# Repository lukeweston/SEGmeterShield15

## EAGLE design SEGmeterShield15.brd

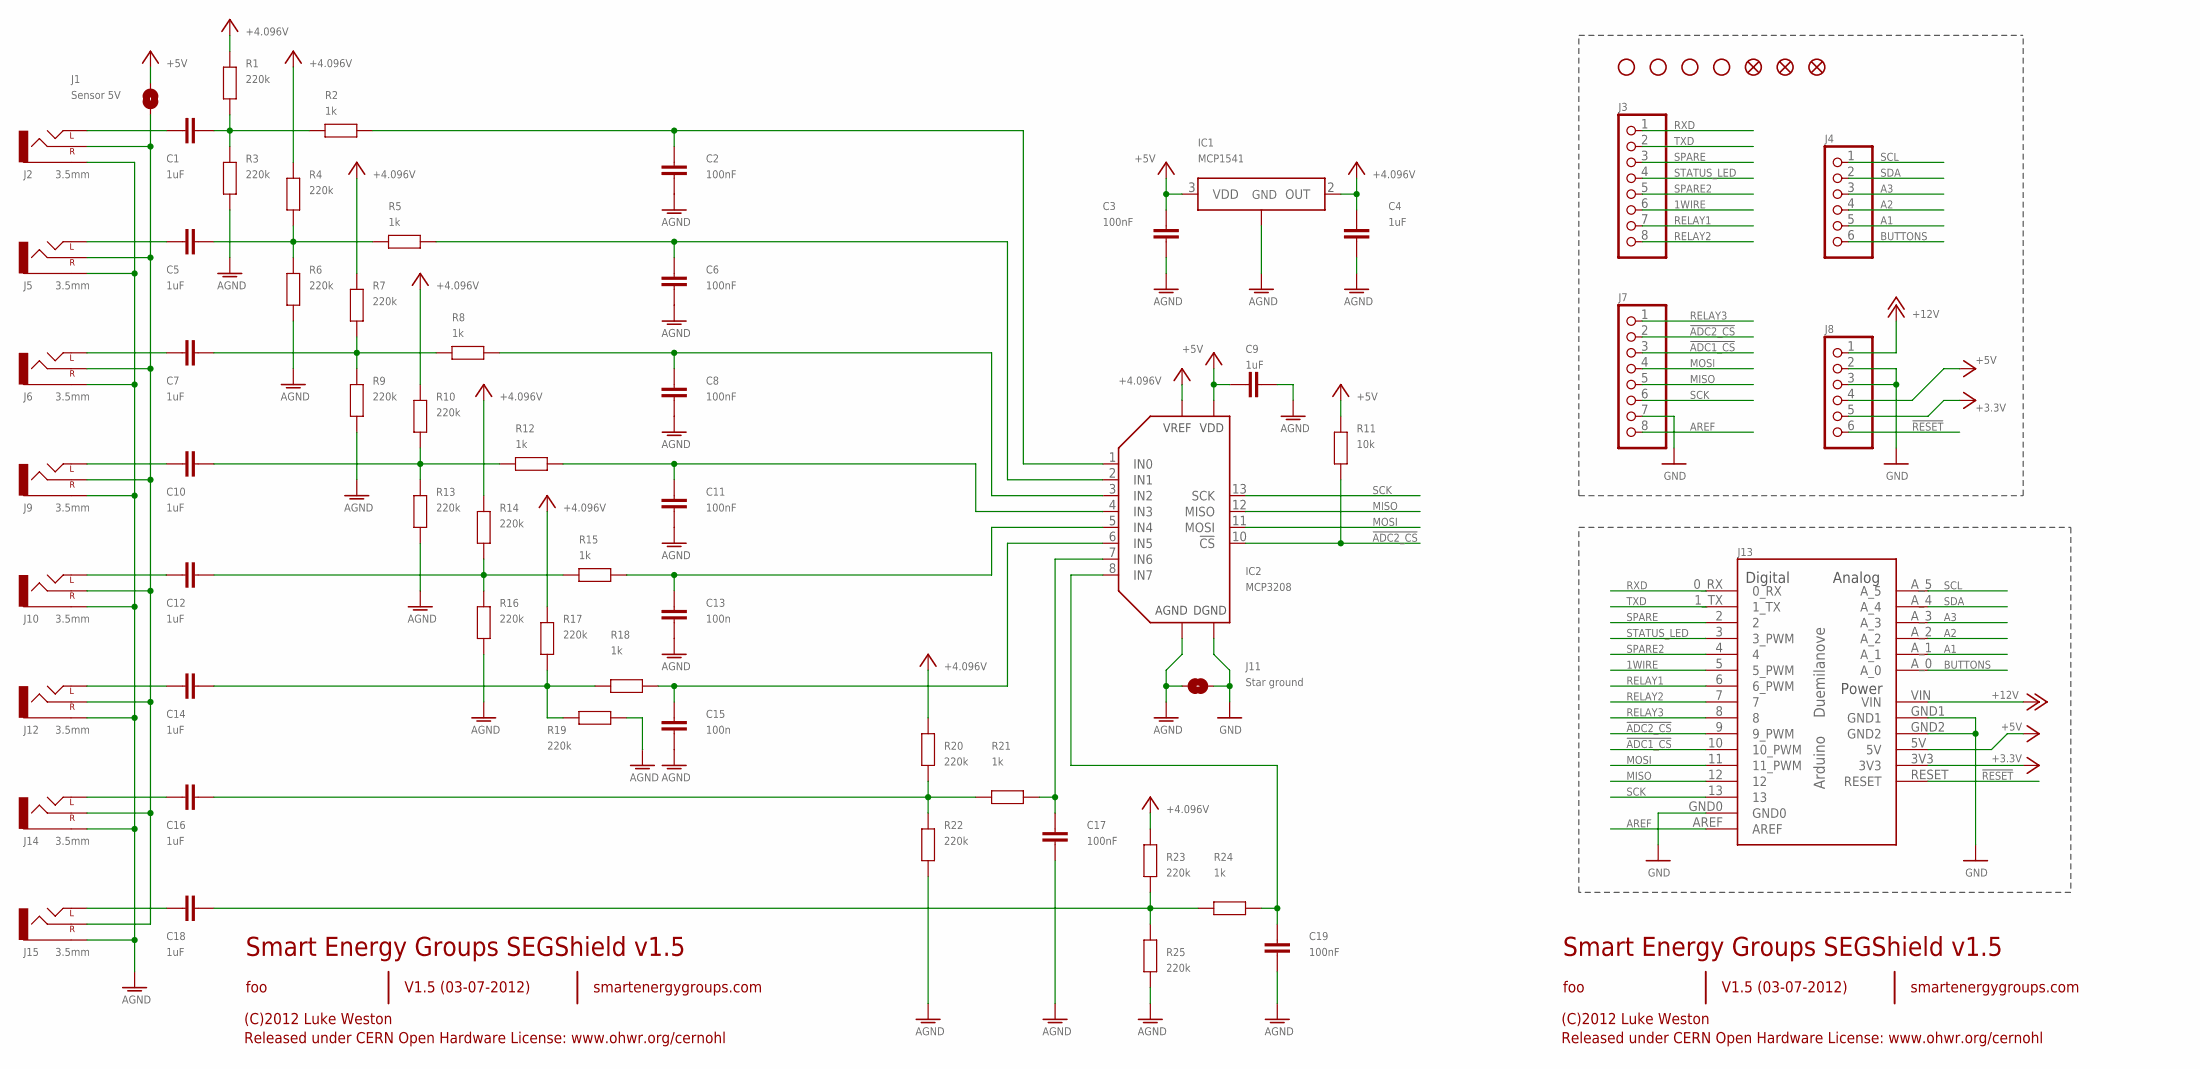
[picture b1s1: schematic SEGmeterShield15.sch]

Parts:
C1, C4, C5, C7, C9, C10, C12, C14, C16, C18: 1uF; 0805
C2, C3, C6, C8, C11, C17, C19: 100nF; 0805
C13, C15: 100n; 0805
IC1: MCP1541; TO92-STRAIGHT
IC2: MCP3208; DIL16
J1: Sensor 5V; SJ
J2, J5, J6, J9, J10, J12, J14, J15: 3.5mm; AUDIO-JACK-3.5MM-SMD
J3, J7: PINHD-1X8; 1X08
J4, J8: PINHD-1X6; 1X06
J11: Star ground; SJ
J13: Arduino-compatible headers; NO-OUTLINE-OCTAGONAL-NOTEXT
JP1, JP2, JP3, JP4: STAND-OFF
JP5, JP6, JP7: FIDUCIAL1.5X3; FIDUCIAL-1.5X3
R1, R3, R4, R6, R7, R9, R10, R13, R14, R16, R17, R19, R20, R22, R23, R25: 220k; 0805
R2, R5, R8, R12, R15, R18, R21, R24: 1k; 0805
R11: 10k; 0805

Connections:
1WIRE: J3.6, J13.5 (5_PWM)
!ADC1_CS: J7.3, J13.10 (10_PWM)
!ADC2_CS: IC2.10 (!CS), J7.2, J13.9 (9_PWM), R11.1
!RESET: J8.6, J13.RESET
+3V3: J8.5, J13.3V3
+5V: C3.2, C9.2, IC1.3 (VDD), IC2.16 (VDD), J1.2, J8.4, J13.5V, R11.2
+12V: J8.1, J13.VIN
A1: J4.5, J13.A_1
A2: J4.4, J13.A_2
A3: J4.3, J13.A_3
AGND: C2.1, C3.1, C4.1, C6.1, C8.1, C9.1, C11.1, C13.1, C15.1, C17.1, C19.1, IC1.1 (GND), IC2.14 (AGND), J2.SLEEVE, J5.SLEEVE, J6.SLEEVE, J9.SLEEVE, J10.SLEEVE, J11.2, J12.SLEEVE, J14.SLEEVE, J15.SLEEVE, R3.1, R6.1, R9.1, R13.1, R16.1, R19.1, R22.1, R25.1
AREF: J7.8, J13.AREF
BUTTONS: J4.6, J13.A_0
GND: IC2.9 (DGND), J7.7, J8.2, J8.3, J11.1, J13.GND0, J13.GND1, J13.GND2
MISO: IC2.12 (MISO), J7.5, J13.12
MOSI: IC2.11 (MOSI), J7.4, J13.11 (11_PWM)
unnamed: C18.1, J15.TIP (LEFT)
unnamed: C16.1, J14.TIP (LEFT)
unnamed: C1.1, J2.TIP (LEFT)
unnamed: C5.1, J5.TIP (LEFT)
unnamed: C14.1, J12.TIP (LEFT)
unnamed: J1.1, J2.RING (RIGHT), J5.RING (RIGHT), J6.RING (RIGHT), J9.RING (RIGHT), J10.RING (RIGHT), J12.RING (RIGHT), J14.RING (RIGHT), J15.RING (RIGHT)
unnamed: C12.1, J10.TIP (LEFT)
unnamed: C10.1, J9.TIP (LEFT)
unnamed: C7.1, J6.TIP (LEFT)
unnamed: C1.2, R1.1, R2.2, R3.2
unnamed: C18.2, R23.1, R24.2, R25.2
unnamed: C16.2, R20.1, R21.2, R22.2
unnamed: C14.2, R17.1, R18.2, R19.2
unnamed: C12.2, R14.1, R15.2, R16.2
unnamed: C5.2, R4.1, R5.2, R6.2
unnamed: C7.2, R7.1, R8.2, R9.2
unnamed: C10.2, R10.1, R12.2, R13.2
unnamed: C17.2, IC2.7 (IN6), R21.1
unnamed: C6.2, IC2.2 (IN1), R5.1
unnamed: C8.2, IC2.3 (IN2), R8.1
unnamed: C11.2, IC2.4 (IN3), R12.1
unnamed: C13.2, IC2.5 (IN4), R15.1
unnamed: C19.2, IC2.8 (IN7), R24.1
unnamed: C15.2, IC2.6 (IN5), R18.1
unnamed: C2.2, IC2.1 (IN0), R2.1
RELAY1: J3.7, J13.6 (6_PWM)
RELAY2: J3.8, J13.7
RELAY3: J7.1, J13.8
RXD: J3.1, J13.0_RX
SCK: IC2.13 (SCK), J7.6, J13.13
SCL: J4.1, J13.A_5
SDA: J4.2, J13.A_4
SPARE: J3.3, J13.2
SPARE2: J3.5, J13.4
STATUS_LED: J3.4, J13.3 (3_PWM)
TXD: J3.2, J13.1_TX
V+: C4.2, IC1.2 (OUT), IC2.15 (VREF), R1.2, R4.2, R7.2, R10.2, R14.2, R17.2, R20.2, R23.2

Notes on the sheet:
Smart Energy Groups SEGShield v1.5
V1.5 (03-07-2012)
foo
(C)2012 Luke Weston
Released under CERN Open Hardware License: www.ohwr.org/cernohl
smartenergygroups.com

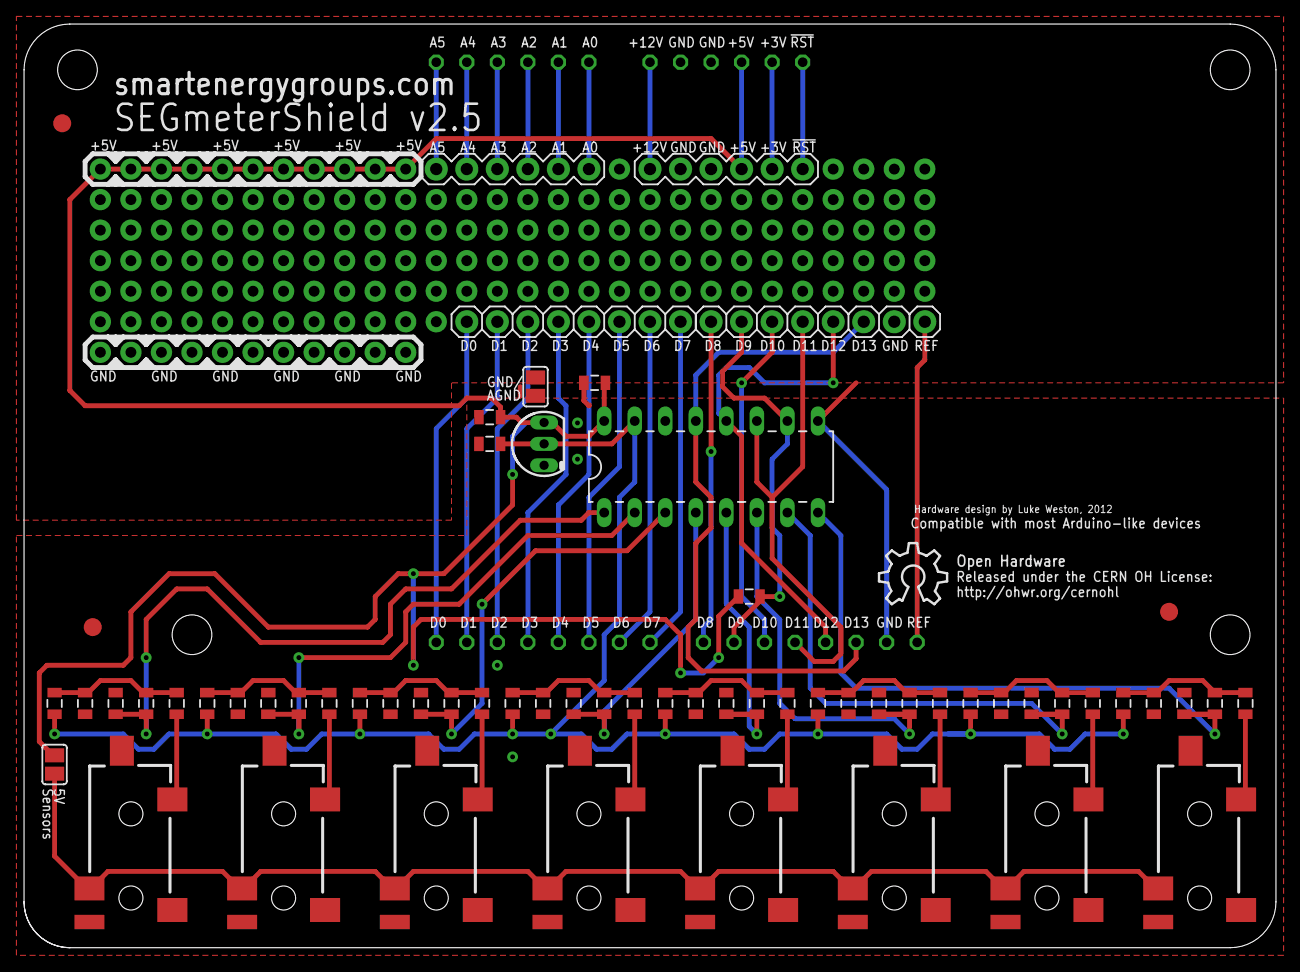
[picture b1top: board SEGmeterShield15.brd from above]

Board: 2 copper layers, 104.1 x 76.8 mm, 69 parts (0 on the bottom side), 53 nets.

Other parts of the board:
U$1: OSHW_8X200_NOTEXT

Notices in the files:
SEGmeterShield15.brd:
Released under the CERN OH License:
